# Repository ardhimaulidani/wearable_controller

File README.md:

Wearable Controller
==============================

Wearable Controller made using ESP32 as base microcontroller with firmware built from FreeRTOS and MicroROS.
Although previously used for drone control in SAFMC 2022 competition, this device is capable to control anything with 6 DoF motion sensing input.
This wearable controller is also equipped with 2 push buttons, 3 channel of analog input, and haptic feedback for intuitive control.

Like its name, wearable controller is able to be used as a regular glove with no additional part or cables outside of the system.
Hardware was built using 3D-Print with design based on real person hands, considering ergonomics and comfortability. 
To avoid unnecessary cables usage, connection of controller and receiver is built based on ESP32 wireless capabilities with MicroROS as communication protocol.

## Usage
### MicroROS
```bash
# Source the ROS 2 installation
source /opt/ros/$ROS_DISTRO/setup.bash

# Create a workspace and download the micro-ROS tools
mkdir microros_ws && cd microros_ws
git clone -b $ROS_DISTRO https://github.com/micro-ROS/micro_ros_setup.git src/micro_ros_setup
sudo apt update && rosdep update
rosdep install --from-path src --ignore-src -y

# Install pip
sudo apt-get install python3-pip

# Build micro-ROS tools and source them
colcon build
source install/local_setup.bash
```

### Create MicroROS-Agent
```bash
# Run micro-ROS-Agent scripts (need internet)
ros2 run micro_ros_setup create_agent_ws.sh

# Build
ros2 run micro_ros_setup build_agent.sh
source install/local_setup.bash
```

### How to Connect
Make sure the device is powered and connected to the same network, then run:
```bash
ros2 run micro_ros_agent micro_ros_agent udp4 --port 8888
```
Press the EN button if device still disconnected from MicroROS-Agent.

## Firmware Development
Installation guide for development usage. Clone exact version of ESP-IDF for the code to be working correctly.
```bash
# Install dependencies
sudo apt-get install git wget flex bison gperf python3 python3-pip python3-setuptools cmake ninja-build ccache libffi-dev libssl-dev dfu-util libusb-1.0-0
pip3 install catkin_pkg lark-parser empy colcon-common-extensions importlib-resources

# Clone ESP-IDF v4.2.2 from sources repo
mkdir -p esp
cd ~/esp
git clone -b v4.2.2 --recursive https://github.com/espressif/esp-idf.git

# Install esp-idf tools
cd ~/esp/esp-idf
./install.sh

# Set up the environment variables
. $HOME/esp/esp-idf/export.sh

# Clone Repo
git clone https://github.com/ardhimaulidani/SAFMC_Wearable.git
cd SAFMC_Wearable/components
git clone https://github.com/micro-ROS/micro_ros_espidf_component
```

Before build edit "micro_ros_espidf_component/colcon.meta" 
```c
        "rmw_microxrcedds": {
            "cmake-args": [
                "-DRMW_UXRCE_XML_BUFFER_LENGTH=400",
                "-DRMW_UXRCE_TRANSPORT=udp",
                "-DRMW_UXRCE_MAX_NODES=1",
                "-DRMW_UXRCE_MAX_PUBLISHERS=3",
                "-DRMW_UXRCE_MAX_SUBSCRIPTIONS=0",
                "-DRMW_UXRCE_MAX_SERVICES=0",
                "-DRMW_UXRCE_MAX_CLIENTS=0",
                "-DRMW_UXRCE_MAX_HISTORY=1"
            ]
        },
        "embeddedrtps": {
            "cmake-args": [
                "-DERTPS_MAX_PUBLISHERS=3",
                "-DERTPS_MAX_SUBSCRIPTIONS=0",
                "-DERTPS_MAX_SERVICES=0",
                "-DERTPS_MAX_CLIENTS=0",
                "-DERTPS_MAX_HISTORY=1"
            ]
        },
```

## How to Change Wearable Device IP and Port
```bash
# Navigate to directory
cd ~/esp/esp-idf/  

# Source esp-idf
. export.sh

# Navigate to git directory
cd SAFMC_Wearable/  

# Initiate build config
idf.py set-target esp32 # use only if program was changed
idf.py menuconfig  

# go to Micro-ROS Settings  
# Change IP Address (check from ifconfig bash)
# Change Port to whatever you want
# Change wifi SSID and password in WiFi Configuration 

# Connect ESP32 programmer to PC
# Get permission on serial access
sudo chmod 666 /dev/ttyUSB0

# Build and Flash
idf.py build  
idf.py flash
```

## References
* [ROS2 to MicroROS](https://medium.com/@SameerT009/connect-esp32-to-ros2-foxy-5f06e0cc64df) : How to connect ESP32 to ROS2 using MicroROS :
* [MicroROS ESP32](https://github.com/micro-ROS/micro_ros_espidf_component) : MicroROS component for ESP32
* [FreeRTOS ESP32](https://docs.espressif.com/projects/esp-idf/en/latest/esp32/api-reference/system/freertos.html) : FreeRTOS documentation on ESP-IDF

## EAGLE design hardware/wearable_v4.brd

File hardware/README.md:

## Wearable Controller Board
This board used for the controller of wearable device  
There are 3 boards that used in this wearable device  
1. Mainboard     : used to place all of the important components   
2. IMU Board     : used to place WT901 IMU sensor on top of the fan  
3. Button Board  : used to place Button according to pilot hand sizes  

You can purchase this wearable from  
>Electronic Specs
````
USB input voltage : 4.5-5.5V
Charging current  : 580mA (changeable using rpog in tp4056 circuit)
Battery           : 3.7V 2000mAh LiPo battery
Min batt voltage  : 3.8V
Max Current       : 230mA
Battery life      : +- 6hours
Wifi Frequency    : 2.4ghz
````
>LED indicator meaning
````
PWR Red LED     : power indicator
STAT Blue LED   : connected
WT901 Green LED : power indicator for imu sensor
STBY Green LED  : battery fully charged
CHRG Red LED    : battery charged
````
>Component List
#### Mainboard  
|Parts Name                           |Parts Number         |Qty  |
|-------------------------------------|---------------------|-----|
|ESP32 Wroom                          |ESP32                |  1  |
|TP4056 Charging IC                   |TP4056               |  1  |
|BA033 Low Dropout voltage regulator  |BA033                |  1  |
|LED 0805                             |PWR, STAT, CHRG, STBY|  4  |
|R330 ohm 0805                        |R2, R4, R5, R6, R7   |  5  |
|R10K ohm 0805                        |R1, R3, R8, R9       |  4  |
|R2K ohm 0805                         |RPROG                |  1  |
|C10uF 0805                           |C2                   |  1  |
|C1uF 0805                            |C1                   |  1  |
|1n4148 smd                           |D1                   |  1  |
|ss8050 sot23 NPN transistor          |Q1                   |  1  |
|SPDT micro switch smd                |SW                   |  1  | 
|USB female micro B                   |J1                   |  1  |
|JST PH2 male female smd connector    |BAT,                 |  1  |
|JST PH3 male female smd connector    |KNTRL                |  1  |
|JST PH4 male female smd connector    |PROG, WT901          |  2  |
#### IMU Board  
|Parts Name                           |Parts Number         |Qty  |
|-------------------------------------|---------------------|-----|
|WT901 IMU Sensor                     |         -           |  1  |
|LED 0805                             |LED1                 |  1  |
|R330 ohm 0805                        |R1                   |  1  |
|JST PH4 male female smd connector    |J1                   |  1  |
#### Button Board  
|Parts Name                           |Parts Number         |Qty  |
|-------------------------------------|---------------------|-----|
|JST PH3 male female smd connector    |J1                   |  1  |
|Silent Push Button 6x6x5mm smd       |SW1, SW2             |  2  |
#### 3D Printed Part
|Parts Name                           |Parts Number         |Qty  |
|-------------------------------------|---------------------|-----|
|Micro vibration motor 3v 10x2mm      |          -          |  1  |
|5v mini fan 30*30mm                  |          -          |  1  |
|10K potentiometer                    |          -          |  3  |

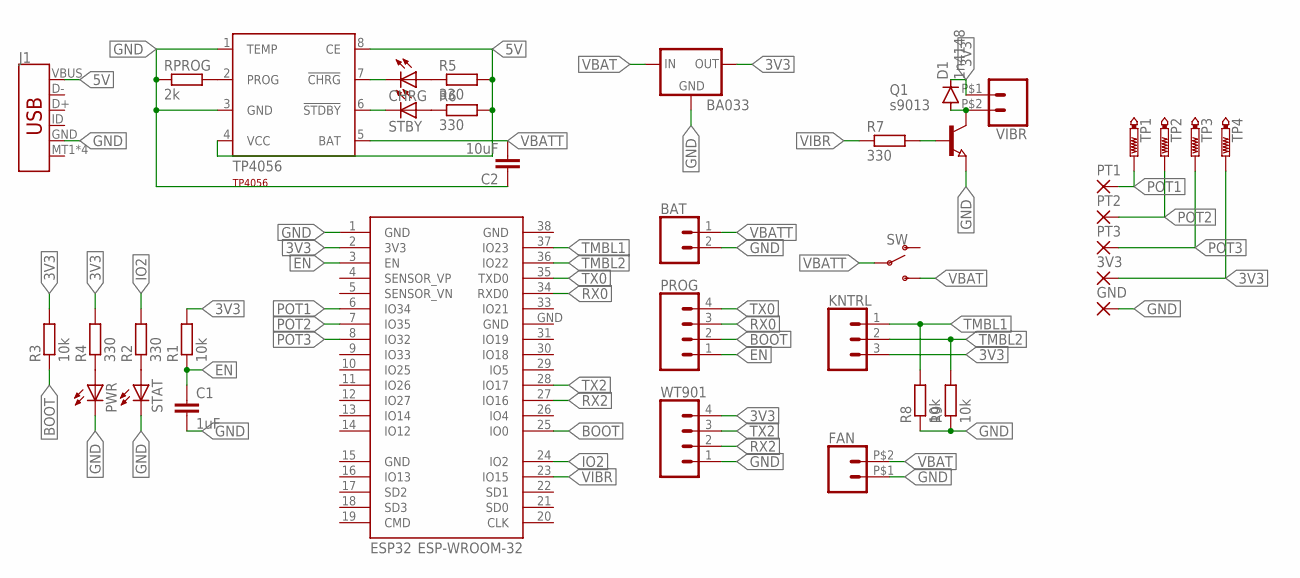
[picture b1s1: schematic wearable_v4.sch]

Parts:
3V3: WIREPADSMD1,27-254; SMD1,27-2,54
BA033: V_REG_78XX7812; TO-252
BAT: CONN_02-JST-2MM-SMT; JST-2-SMD
C1: 1uF; C0805
C2: 10uF; C0805
CHRG: LEDCHIPLED_0805; CHIPLED_0805
D1: 1n4148; SOD80C
ESP32: ESP-WROOM-32
FAN: SOLDER_PAD_2
GND: WIREPADSMD1,27-254; SMD1,27-2,54
J1: USB_MICRO-B_SMT; USB-MICROB
KNTRL: 3-PIN SMD; JST-3-SMD
PROG: CONN_04JST-SMD; JST-4-SMD
PT1, PT2, PT3: WIREPADSMD1,27-254; SMD1,27-2,54
PWR: LEDCHIPLED_0805; CHIPLED_0805
Q1: s9013; SOT23
R1, R3, R8, R9: 10k; R0805
R2, R4, R5, R6, R7: 330; R0805
RPROG: 2k; R0805
STAT: LEDCHIPLED_0805; CHIPLED_0805
STBY: LEDCHIPLED_0805; CHIPLED_0805
SW: SWITCH-SPDT-SMD-RIGHT-ANGLE; SWITCH_SPST_SMD_A
TP1, TP2, TP3, TP4: PTR1TP09R; TP09R
TP4056: TP4056; SOT23-8
VIBR: SOLDER_PAD_2
WT901: CONN_04JST-SMD; JST-4-SMD

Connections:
3V3: 3V3.1, BA033.2 (OUT), D1.C, ESP32.2 (3V3), KNTRL.3 (1), R1.2, R3.2, R4.2, TP4.TP, VIBR.P$1 (1), WT901.4
5V: J1.VBUS, R5.2, R6.2, TP4056.4 (VCC), TP4056.8 (CE)
BOOT: ESP32.25 (IO0), PROG.2, R3.1
EN: C1.1, ESP32.3 (EN), PROG.1, R1.1
GND: BA033.3 (GND), BAT.2 (1), C1.2, C2.1, ESP32.1 (GND), ESP32.15 (GND), ESP32.38 (GND), ESP32.GND, FAN.P$1 (1), GND.1, J1.GND, PWR.C, Q1.2 (E), R8.1, R9.1, RPROG.1, STAT.C, TP4056.1 (TEMP), TP4056.3 (GND), WT901.1
IO2: ESP32.24 (IO2), R2.2
unnamed: R2.1, STAT.A
unnamed: PWR.A, R4.1
unnamed: CHRG.A, R5.1
unnamed: R6.1, STBY.A
unnamed: CHRG.C, TP4056.7 (!CHRG)
unnamed: STBY.C, TP4056.6 (!STDBY)
unnamed: RPROG.2, TP4056.2 (PROG)
unnamed: Q1.1 (B), R7.2
unnamed: D1.A, Q1.3 (C), VIBR.P$2 (2)
POT1: ESP32.6 (IO34), PT1.1, TP1.TP
POT2: ESP32.7 (IO35), PT2.1, TP2.TP
POT3: ESP32.8 (IO32), PT3.1, TP3.TP
RX0: ESP32.34 (RXD0), PROG.3
RX2: ESP32.27 (IO16), WT901.2
TMBL1: ESP32.37 (IO23), KNTRL.1 (3), R8.2
TMBL2: ESP32.36 (IO22), KNTRL.2, R9.2
TX0: ESP32.35 (TXD0), PROG.4
TX2: ESP32.28 (IO17), WT901.3
VBAT: BA033.1 (IN), FAN.P$2 (2), SW.3 (S)
VBATT: BAT.1 (2), C2.2, SW.2, TP4056.5 (BAT)
VIBR: ESP32.23 (IO15), R7.1

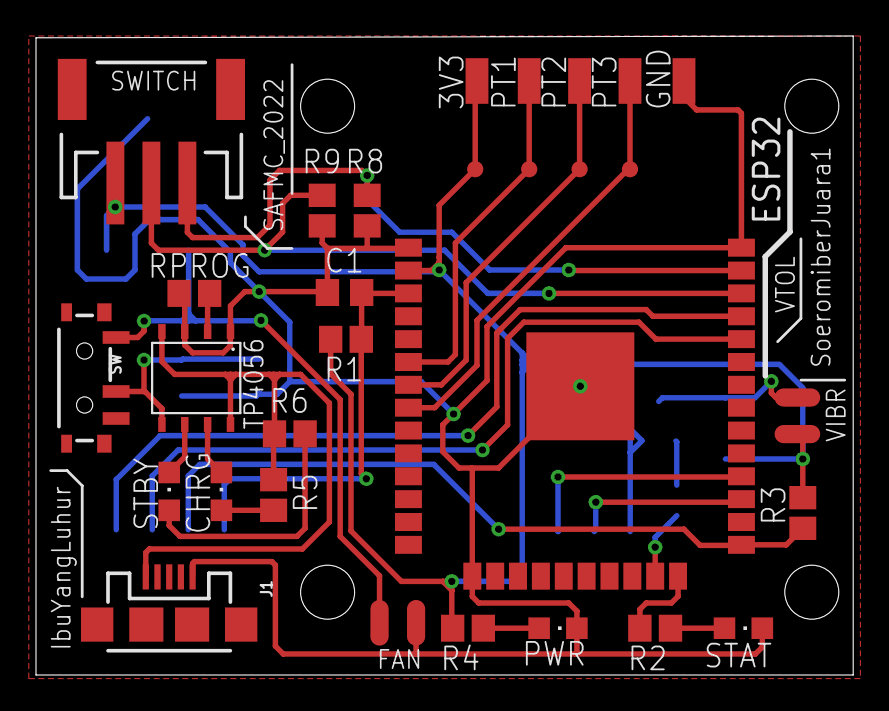
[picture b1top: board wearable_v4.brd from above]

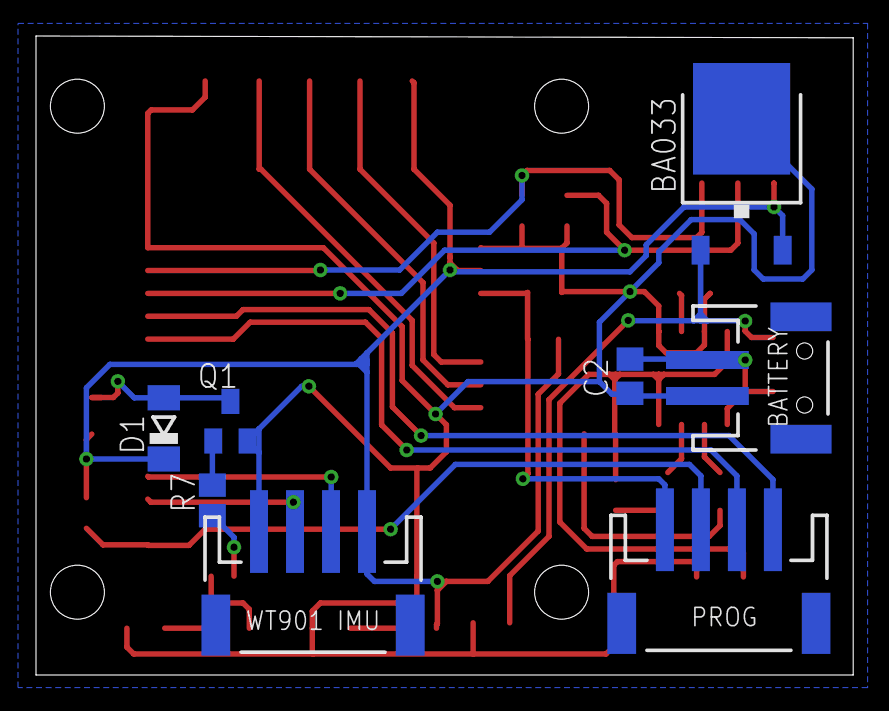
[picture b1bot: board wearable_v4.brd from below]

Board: 2 copper layers, 45.4 x 35.5 mm, 38 parts (8 on the bottom side), 27 nets.

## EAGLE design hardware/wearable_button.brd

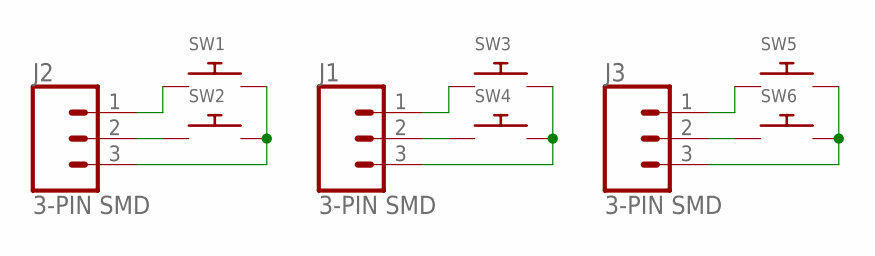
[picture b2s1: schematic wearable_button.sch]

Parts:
J1, J2, J3: 3-PIN SMD; JST-3-SMD
SW1, SW2, SW3, SW4, SW5, SW6: SWITCH_PUSHBUTTONSOFTTOUCHSMD_SJ; PUSHBUTTON_SMD_SJ

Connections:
unnamed: J2.2, SW2.P$1
unnamed: J2.1 (3), SW1.P$1
unnamed: J1.1 (3), SW3.P$1
unnamed: J1.2, SW4.P$1
unnamed: J2.3 (1), SW1.P$2, SW2.P$2
unnamed: J1.3 (1), SW3.P$2, SW4.P$2
unnamed: J3.3 (1), SW5.P$2, SW6.P$2
unnamed: J3.1 (3), SW5.P$1
unnamed: J3.2, SW6.P$1

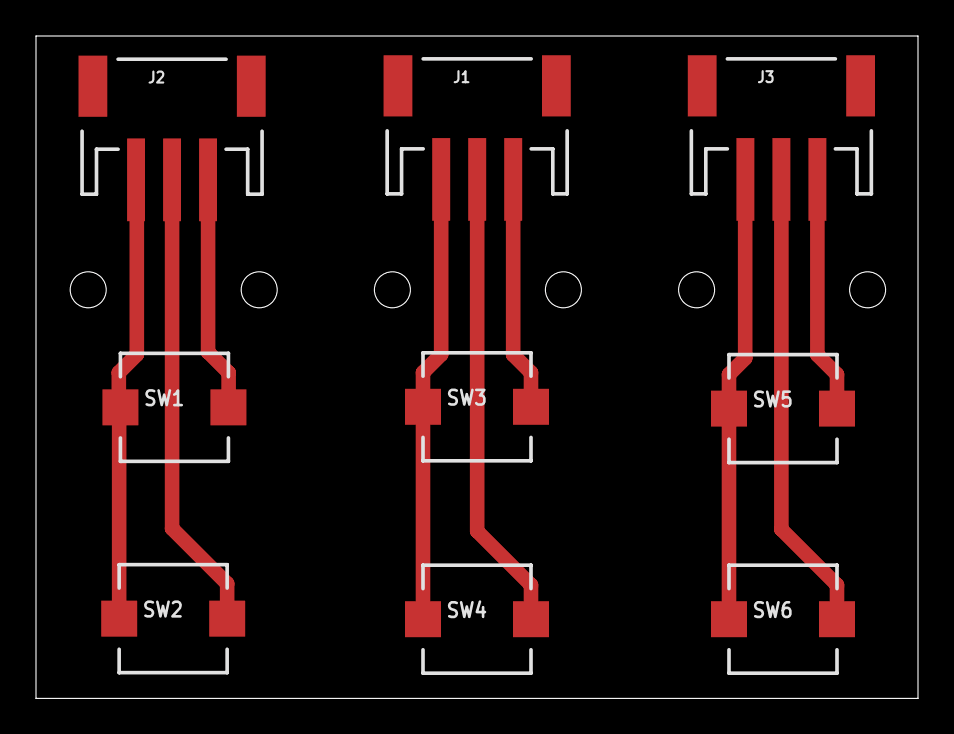
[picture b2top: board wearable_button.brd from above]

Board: 2 copper layers, 49.0 x 36.8 mm, 9 parts (0 on the bottom side), 9 nets.

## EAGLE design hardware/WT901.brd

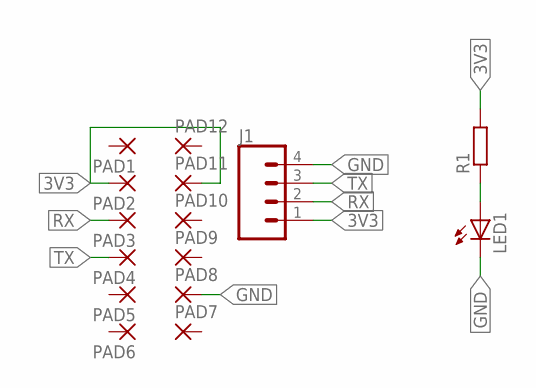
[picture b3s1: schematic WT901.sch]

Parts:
J1: CONN_04JST-SMD; JST-4-SMD
LED1: LEDCHIPLED_0805; CHIPLED_0805
PAD1, PAD2, PAD3, PAD4, PAD5, PAD6, PAD7, PAD8, PAD9, PAD10, PAD11, PAD12: SMD2; SMD1,27-2,54
R1: R-EU_R0805; R0805

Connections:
3V3: J1.1, PAD2.1, PAD11.1, R1.2
GND: J1.4, LED1.C, PAD8.1
unnamed: LED1.A, R1.1
RX: J1.2, PAD3.1
TX: J1.3, PAD4.1

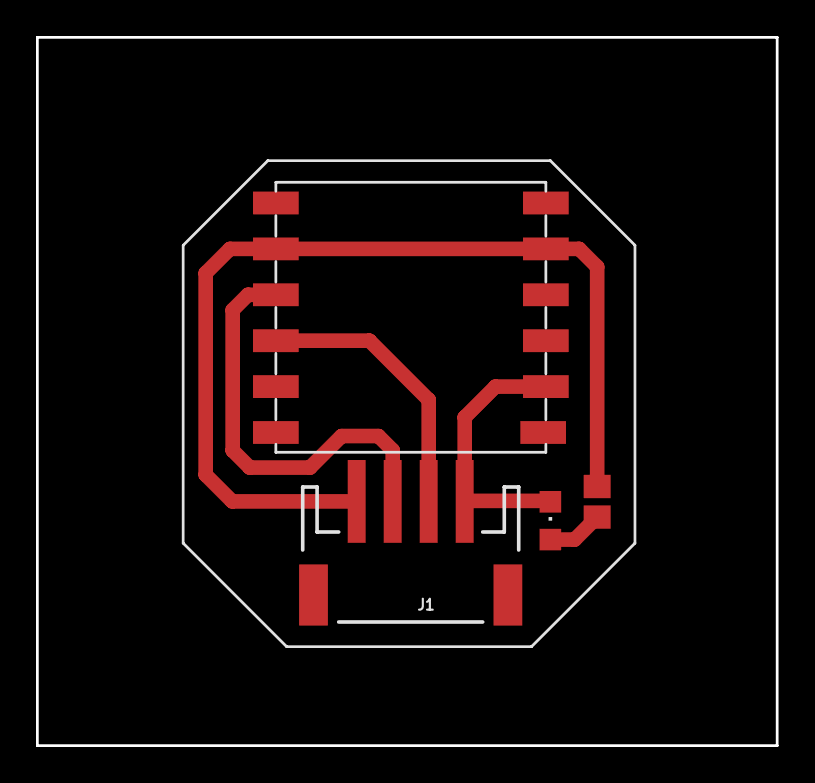
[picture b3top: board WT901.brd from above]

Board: 2 copper layers, 41.1 x 39.4 mm, 15 parts (0 on the bottom side), 5 nets.

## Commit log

2022-02-17 Masuk Git
2024-03-16 update latest documentation

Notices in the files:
parts and their libraries:
SparkFun-Connectors: Licensing: Creative Commons ShareAlike 4.0 International - https://creativecommons.org/licenses/by-sa/4.0
esp32: Creative Commons Attribution-ShareAlike 4.0 International
